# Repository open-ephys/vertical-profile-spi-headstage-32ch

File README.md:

# vertical-profile-spi-headstage-32ch
Design files of a 32 channels headstage.

## Licensing

The designs, documentation, and photos available in this repository are free: you can redistribute it and/or modify it under the terms of the used license.
Check the file named LICENSE.

<br />This work is licensed under a <a rel="license" href="http://creativecommons.org/licenses/by-nc-sa/3.0/igo/">Creative Commons Attribution-NonCommercial-ShareAlike 3.0 IGO License</a>.

[1]: https://docs.google.com/spreadsheets/d/1aobmmEzBDethzIlrm1eg0eYkBqlyX3s9WbA9KgRwVQI/edit?usp=sharing

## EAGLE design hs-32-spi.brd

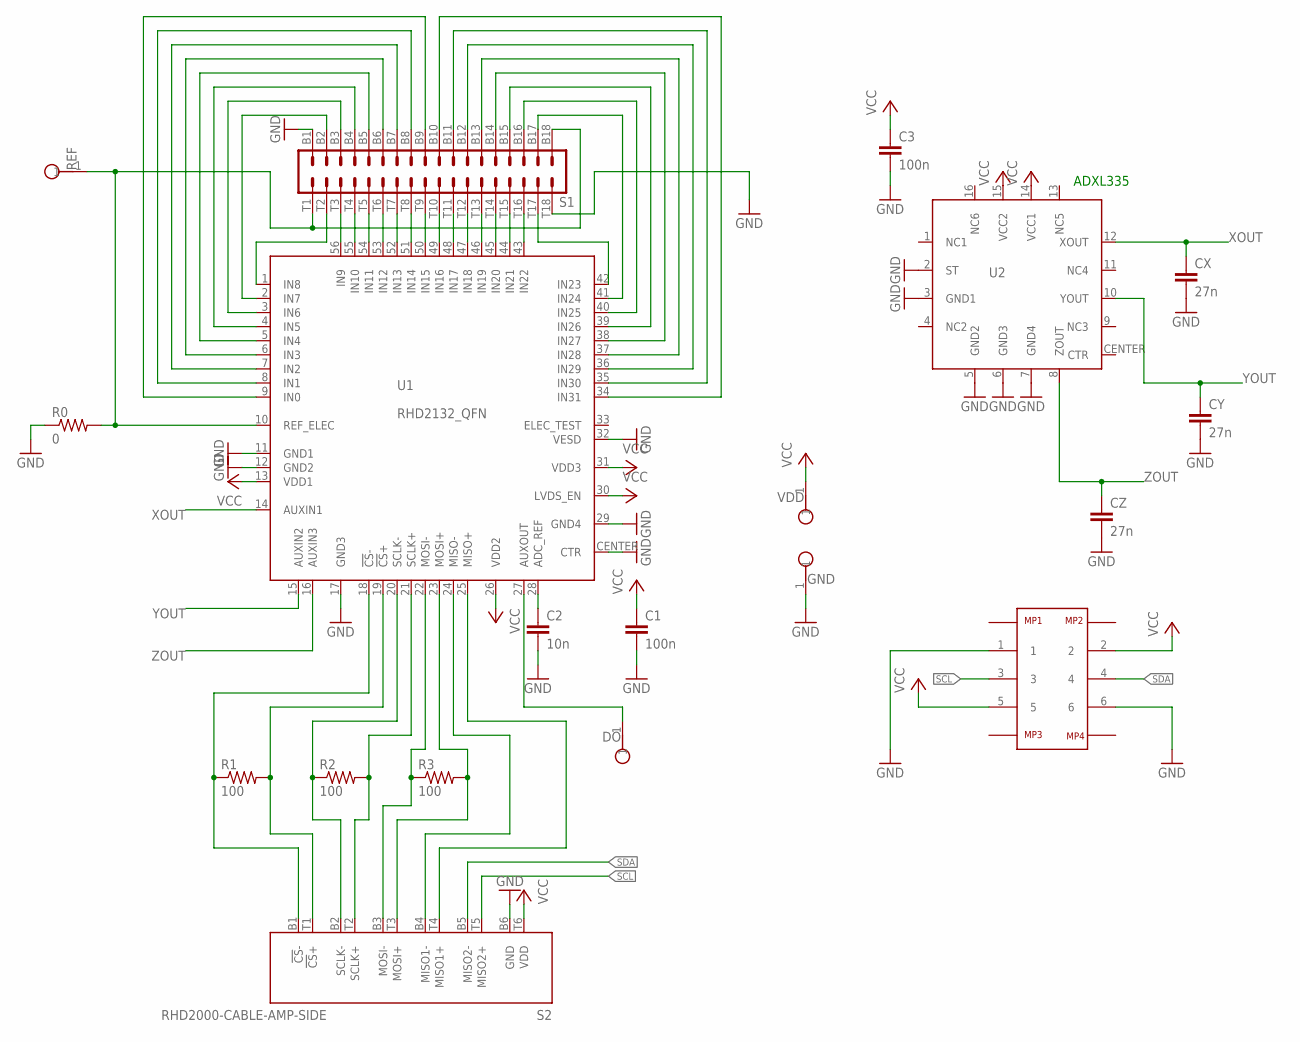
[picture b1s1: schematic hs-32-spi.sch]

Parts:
C1, C3: 100n; 0402
C2: 10n; 0402
CX: 27n; 0402
CY: 27n; 0402
CZ: 27n; 0402
DO: TESTPOINT_SMALL
GND: TESTPOINT_SMALL
R0: 0; 0402
R1, R2, R3: 100; 0201
REF: TESTPOINT_SMALL
S1: OMNETICS_A79025
S2: RHD2000-CABLE-AMP-SIDE; OMNETICS_PZN-12-AA
U1: RHD2132_QFN; QFN56_8_X_8_LARGE
U2: ADXL335
U3: MOLEX_5050700622
VDD: TESTPOINT_SMALL

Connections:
GND: C1.2, C2.2, C3.2, CX.2, CY.2, CZ.2, GND.1, R0.1, S1.B1, S1.T18, S2.B6 (GND), U1.11 (GND1), U1.12 (GND2), U1.17 (GND3), U1.29 (GND4), U1.32 (VESD), U1.CENTER (CTR), U2.2 (ST), U2.3 (GND1), U2.5 (GND2), U2.6 (GND3), U2.7 (GND4), U3.1, U3.6
unnamed: R0.2, REF.1, S1.B18, S1.T1, U1.10 (REF_ELEC)
unnamed: S1.B3, U1.3 (IN6)
unnamed: S1.B2, U1.2 (IN7)
unnamed: S1.B4, U1.4 (IN5)
unnamed: S1.B5, U1.5 (IN4)
unnamed: S1.B6, U1.6 (IN3)
unnamed: S1.B7, U1.7 (IN2)
unnamed: S1.B8, U1.8 (IN1)
unnamed: S1.B9, U1.9 (IN0)
unnamed: S1.B10, U1.34 (IN31)
unnamed: R1.1, S2.B1 (!CS!-), U1.18 (!CS!-)
unnamed: S1.B17, U1.41 (IN24)
unnamed: S1.B16, U1.40 (IN25)
unnamed: S1.B15, U1.39 (IN26)
unnamed: S1.B14, U1.38 (IN27)
unnamed: S1.B13, U1.37 (IN28)
unnamed: S1.B12, U1.36 (IN29)
unnamed: S1.B11, U1.35 (IN30)
unnamed: S1.T9, U1.50 (IN15)
unnamed: S1.T8, U1.51 (IN14)
unnamed: S1.T7, U1.52 (IN13)
unnamed: S1.T3, U1.56 (IN9)
unnamed: S1.T4, U1.55 (IN10)
unnamed: S1.T5, U1.54 (IN11)
unnamed: S1.T6, U1.53 (IN12)
unnamed: S1.T10, U1.49 (IN16)
unnamed: S1.T11, U1.48 (IN17)
unnamed: S1.T12, U1.47 (IN18)
unnamed: S1.T13, U1.46 (IN19)
unnamed: S1.T14, U1.45 (IN20)
unnamed: S1.T15, U1.44 (IN21)
unnamed: S1.T16, U1.43 (IN22)
unnamed: S1.T2, U1.1 (IN8)
unnamed: S1.T17, U1.42 (IN23)
unnamed: R1.2, S2.T1 (!CS!+), U1.19 (!CS!+)
unnamed: R2.1, S2.B2 (SCLK-), U1.20 (SCLK-)
unnamed: R2.2, S2.T2 (SCLK+), U1.21 (SCLK+)
unnamed: R3.1, S2.B3 (MOSI-), U1.22 (MOSI-)
unnamed: R3.2, S2.T3 (MOSI+), U1.23 (MOSI+)
unnamed: S2.B4 (MISO1-), U1.24 (MISO-)
unnamed: S2.T4 (MISO1+), U1.25 (MISO+)
unnamed: C2.1, U1.28 (ADC_REF)
unnamed: DO.1, U1.27 (AUXOUT)
SCL: S2.T5 (MISO2+), U3.3
SDA: S2.B5 (MISO2-), U3.4
VCC: C1.1, C3.1, S2.T6 (VDD), U1.13 (VDD1), U1.26 (VDD2), U1.30 (LVDS_EN), U1.31 (VDD3), U2.14 (VCC1), U2.15 (VCC2), U3.2, U3.5, VDD.1
XOUT: CX.1, U1.14 (AUXIN1), U2.12 (XOUT)
YOUT: CY.1, U1.15 (AUXIN2), U2.10 (YOUT)
ZOUT: CZ.1, U1.16 (AUXIN3), U2.8 (ZOUT)

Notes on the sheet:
ADXL335

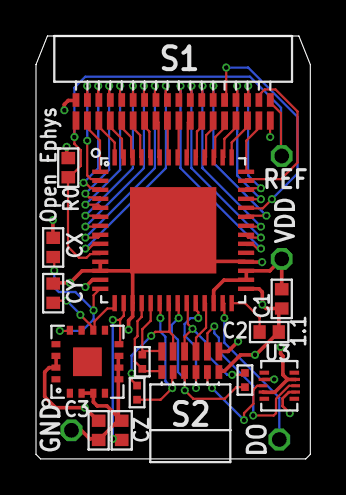
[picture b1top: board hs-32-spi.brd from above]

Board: 4 copper layers, 15.2 x 23.5 mm, 20 parts (1 on the bottom side), 50 nets.

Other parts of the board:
X: OE-LOGO_3.5X2.5; OE-LOGO-3.5X2.5

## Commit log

2025-02-13 Added license and readme.
2025-02-13 Added design files.
2025-02-13 Added initial attempt of adding an expansion connector.
2025-02-13 Added .gitignore.
2025-02-13 Reorganize files.
2025-03-03 Changed location of Omnetics connector closer to headstage center.
    . This allowed space to move the new expansion connector to a position where there's no need to increase the headstage size.
    TO DO
    . Complete the layout.
2025-03-04 Finished layout for v1.1
2025-03-04 Fixed library.
2025-03-04 Added production files
